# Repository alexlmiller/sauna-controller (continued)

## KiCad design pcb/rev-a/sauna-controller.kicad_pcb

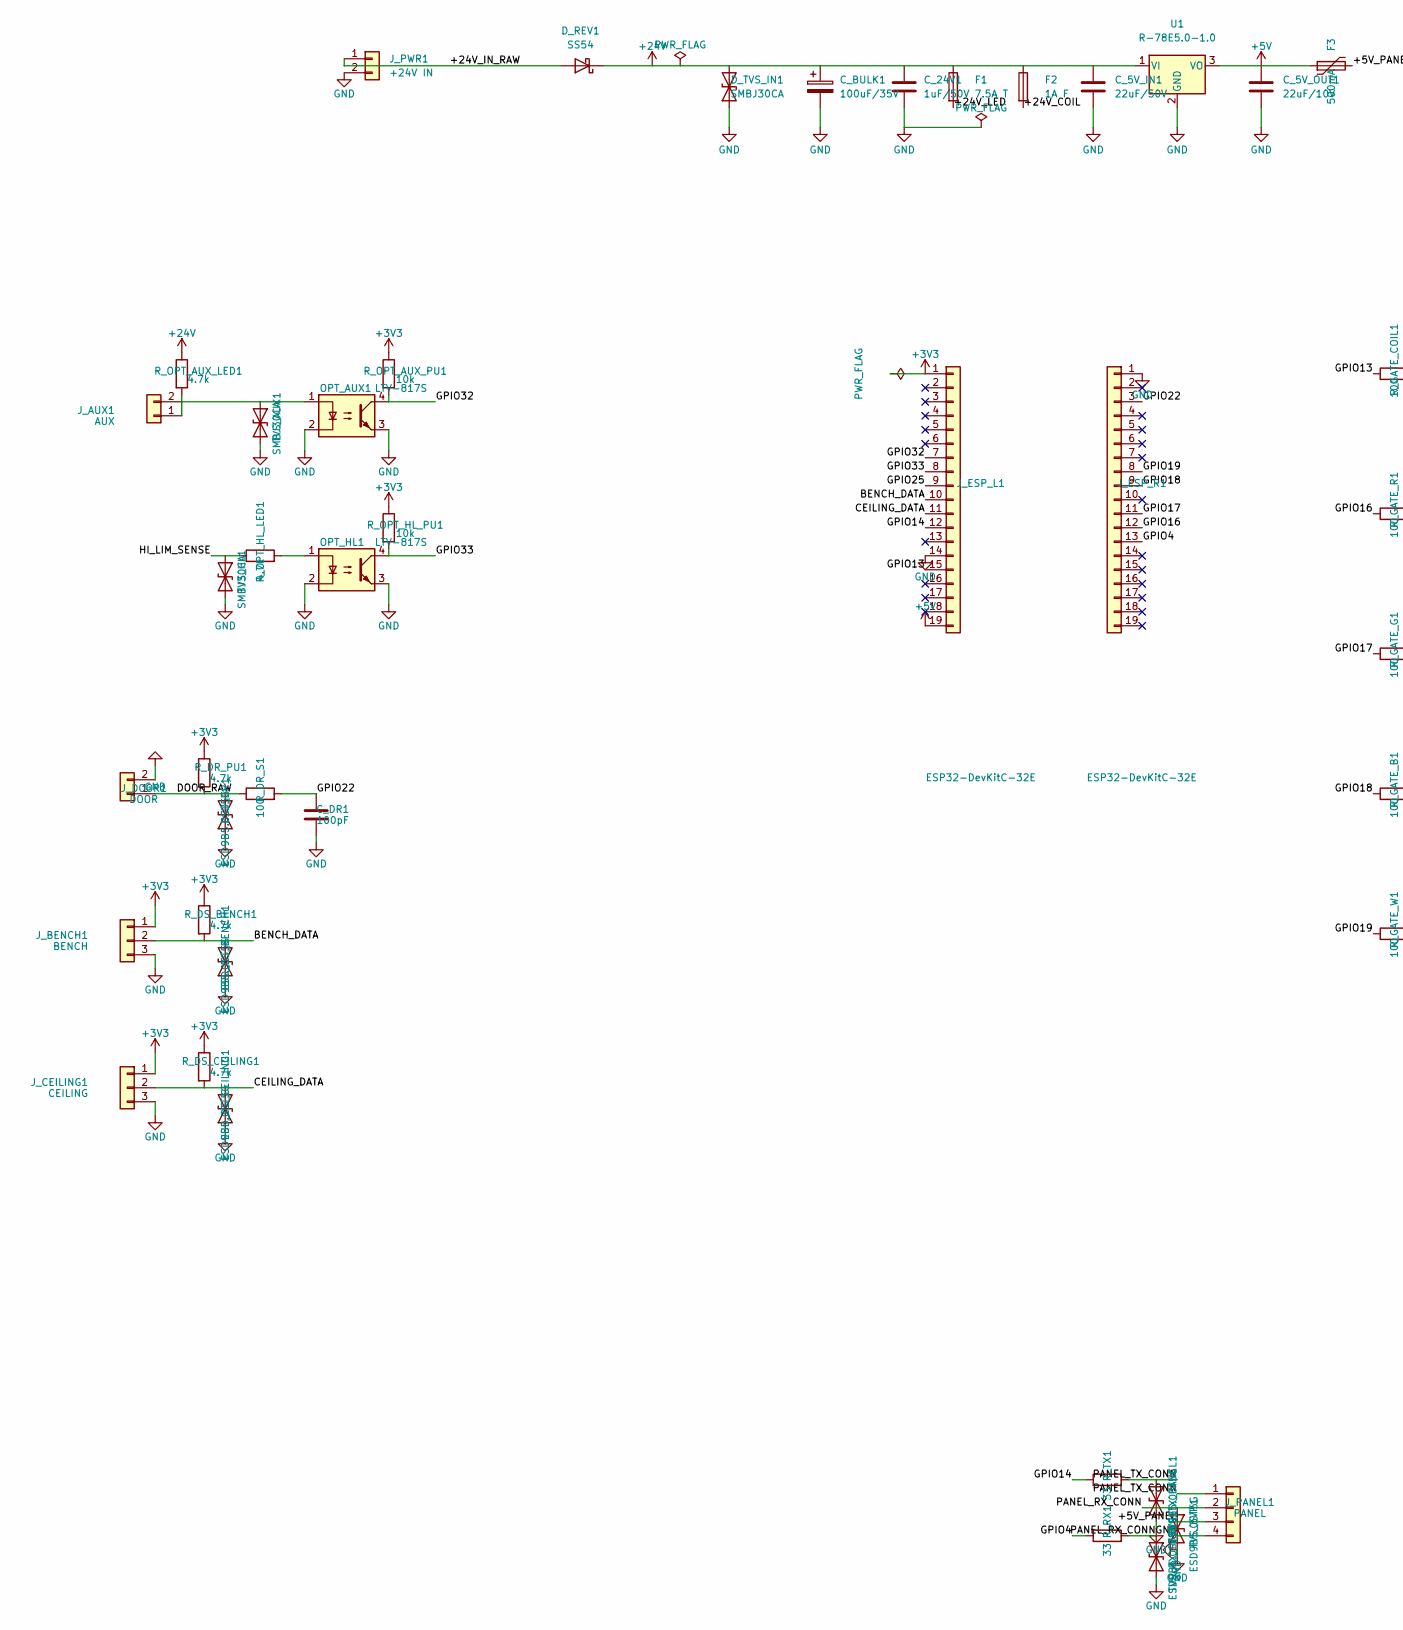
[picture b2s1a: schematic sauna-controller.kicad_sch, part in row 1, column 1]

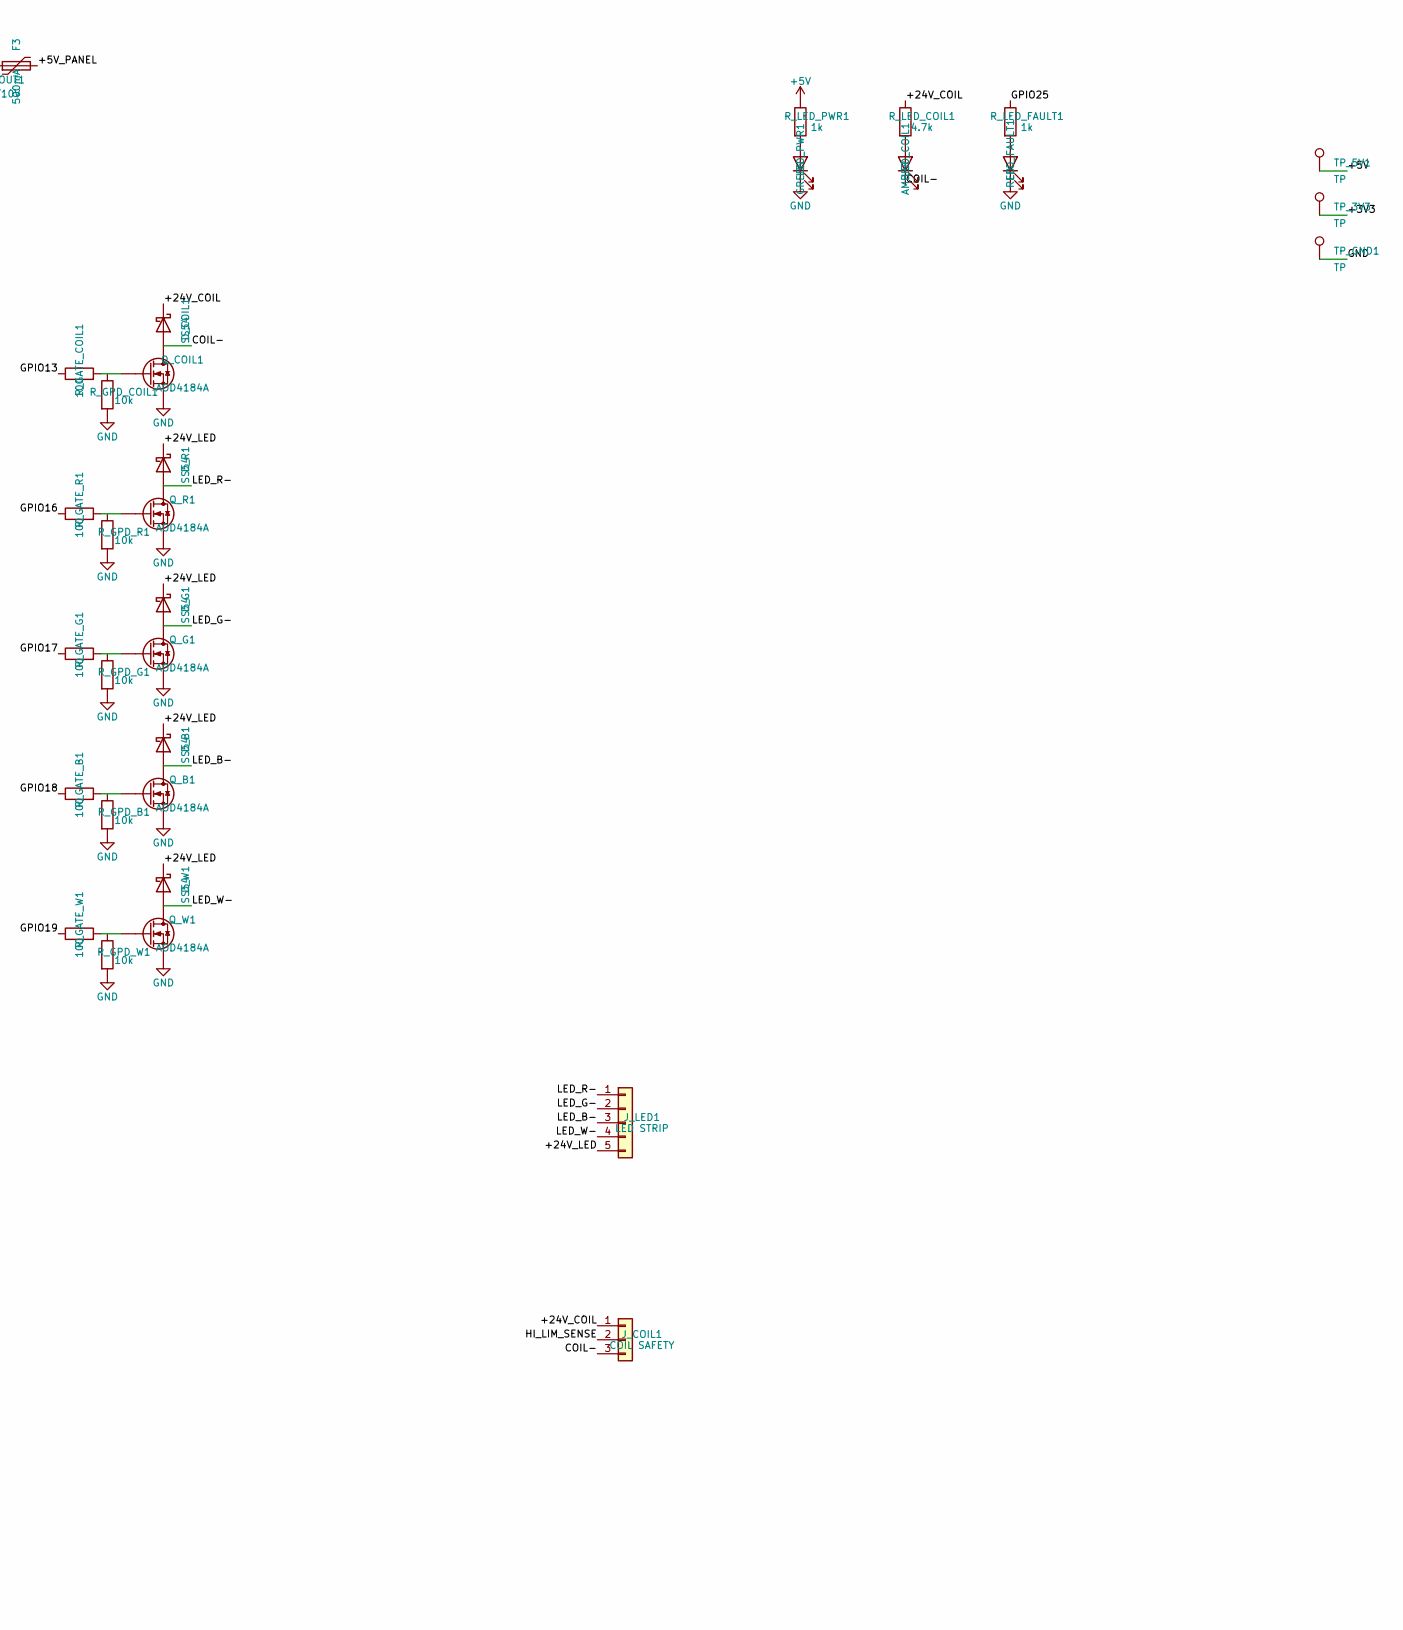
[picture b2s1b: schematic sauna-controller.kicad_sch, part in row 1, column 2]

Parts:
C_5V_IN1: 22uF/50V; C_1210_3225Metric
C_5V_OUT1: 22uF/10V; C_0805_2012Metric
C_24V1: 1uF/50V; C_0805_2012Metric
C_BULK1: 100uF/35V; CP_Radial_D8.0mm_P3.50mm
C_DR1: 100pF; C_0805_2012Metric
D_B1: SS54; D_SMA
D_COIL1: SS54; D_SMA
D_G1: SS54; D_SMA
D_R1: SS54; D_SMA
D_REV1: SS54; D_SMA
D_TVS_IN1: SMBJ30CA; D_SMB
D_W1: SS54; D_SMA
ESD_DR1: ESD9B5.0ST5G; D_SOD-323
ESD_DS_BENCH1: ESD9B5.0ST5G; D_SOD-323
ESD_DS_CEILING1: ESD9B5.0ST5G; D_SOD-323
F1: 7.5A T; Fuseholder_Clip-5x20mm_Schurter_OG_Lateral_P15.00x5.00mm_D1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
F2: 1A F; Fuseholder_Clip-5x20mm_Schurter_OG_Lateral_P15.00x5.00mm_D1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
F3: 500mA; R_1812_4532Metric
J_AUX1: AUX; TerminalBlock_Phoenix_MKDS-1,5-2-5.08_1x02_P5.08mm_Horizont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
J_BENCH1: BENCH; TerminalBlock_Phoenix_MKDS-1,5-3-5.08_1x03_P5.08mm_Horizont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
J_CEILING1: CEILING; TerminalBlock_Phoenix_MKDS-1,5-3-5.08_1x03_P5.08mm_Horizont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
J_COIL1: COIL SAFETY; TerminalBlock_Phoenix_MKDS-1,5-3-5.08_1x03_P5.08mm_Horizont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
J_DOOR1: DOOR; TerminalBlock_Phoenix_MKDS-1,5-2-5.08_1x02_P5.08mm_Horizont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
J_ESP_L1: ESP32-DevKitC-32E; PinSocket_1x19_P2.54mm_Vertical
J_ESP_R1: ESP32-DevKitC-32E; PinSocket_1x19_P2.54mm_Vertical
J_LED1: LED STRIP; TerminalBlock_Phoenix_MKDS-1,5-5-5.08_1x05_P5.08mm_Horizont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
J_PANEL1: PANEL; TerminalBlock_Phoenix_MKDS-1,5-4-5.08_1x04_P5.08mm_Horizont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
J_PWR1: +24V IN; TerminalBlock_Phoenix_MKDS-1,5-2-5.08_1x02_P5.08mm_Horizont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
LED_COIL1: AMBER; LED_0805_2012Metric
LED_FAULT1: RED; LED_0805_2012Metric
LED_PWR1: GREEN; LED_0805_2012Metric
OPT_AUX1: LTV-817S; DIP-4_W7.62mm
OPT_HL1: LTV-817S; DIP-4_W7.62mm
Q_B1: AOD4184A; TO-252-2
Q_COIL1: AOD4184A; TO-252-2
Q_G1: AOD4184A; TO-252-2
Q_R1: AOD4184A; TO-252-2
Q_W1: AOD4184A; TO-252-2
R_DR_PU1: 4.7k; R_0805_2012Metric
R_DR_S1: 100; R_0805_2012Metric
R_DS_BENCH1: 4.7k; R_0805_2012Metric
R_DS_CEILING1: 4.7k; R_0805_2012Metric
R_GATE_B1: 100; R_0805_2012Metric
R_GATE_COIL1: 100; R_0805_2012Metric
R_GATE_G1: 100; R_0805_2012Metric
R_GATE_R1: 100; R_0805_2012Metric
R_GATE_W1: 100; R_0805_2012Metric
R_GPD_B1: 10k; R_0805_2012Metric
R_GPD_COIL1: 10k; R_0805_2012Metric
R_GPD_G1: 10k; R_0805_2012Metric
R_GPD_R1: 10k; R_0805_2012Metric
R_GPD_W1: 10k; R_0805_2012Metric
R_LED_COIL1: 4.7k; R_0805_2012Metric
R_LED_FAULT1: 1k; R_0805_2012Metric
R_LED_PWR1: 1k; R_0805_2012Metric
R_OPT_AUX_LED1: 4.7k; R_0805_2012Metric
R_OPT_AUX_PU1: 10k; R_0805_2012Metric
R_OPT_HL_LED1: 4.7k; R_0805_2012Metric
R_OPT_HL_PU1: 10k; R_0805_2012Metric
R_RX1: 33; R_0805_2012Metric
R_TX1: 33; R_0805_2012Metric
TP_3V3, TP_5V1: TP; TestPoint_Pad_D1.5mm
TP_GND1: TP; TestPoint_Pad_D1.5mm
TVS_5VP1: ESD9B5.0ST5G; D_SOD-323
TVS_AUX1: SMBJ30CA; D_SMB
TVS_HL1: SMBJ30CA; D_SMB
TVS_RX_PANEL1: ESD9B5.0ST5G; D_SOD-323
TVS_TX_PANEL1: ESD9B5.0ST5G; D_SOD-323
U1: R-78E5.0-1.0; Converter_DCDC_RECOM_R-78E-0.5_THT

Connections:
+3V3: J_BENCH1.1, J_CEILING1.1, J_ESP_L1.1, R_DR_PU1.1, R_DS_BENCH1.1, R_DS_CEILING1.1, R_OPT_AUX_PU1.1, R_OPT_HL_PU1.1, TP_3V3.1 (1_1)
+5V: C_5V_OUT1.1, F3.1, J_ESP_L1.19, R_LED_PWR1.1, TP_5V1.1 (1_1), U1.3 (VO)
+24V: C_5V_IN1.1, C_24V1.1, C_BULK1.1, D_REV1.1 (K), D_TVS_IN1.2 (A2), F1.1, F2.1, R_OPT_AUX_LED1.1, U1.1 (VI)
/+5V_PANEL: F3.2, J_PANEL1.3
/+24V_COIL: D_COIL1.1 (K), F2.2, J_COIL1.1, R_LED_COIL1.1
/+24V_IN_RAW: D_REV1.2 (A), J_PWR1.1
/+24V_LED: D_B1.1 (K), D_G1.1 (K), D_R1.1 (K), D_W1.1 (K), F1.2, J_LED1.5
/BENCH_DATA: ESD_DS_BENCH1.2 (A2), J_BENCH1.2, J_ESP_L1.10, R_DS_BENCH1.2
/CEILING_DATA: ESD_DS_CEILING1.2 (A2), J_CEILING1.2, J_ESP_L1.11, R_DS_CEILING1.2
/COIL-: D_COIL1.2 (A), J_COIL1.3, LED_COIL1.1 (K), Q_COIL1.2 (D)
/DOOR_RAW: ESD_DR1.2 (A2), J_DOOR1.1, R_DR_PU1.2, R_DR_S1.1
/GPIO4: J_ESP_R1.13, R_RX1.1
/GPIO13: J_ESP_L1.15, R_GATE_COIL1.1
/GPIO14: J_ESP_L1.12, R_TX1.1
/GPIO16: J_ESP_R1.12, R_GATE_R1.1
/GPIO17: J_ESP_R1.11, R_GATE_G1.1
/GPIO18: J_ESP_R1.9, R_GATE_B1.1
/GPIO19: J_ESP_R1.8, R_GATE_W1.1
/GPIO22: C_DR1.1, J_ESP_R1.3, R_DR_S1.2
/GPIO25: J_ESP_L1.9, R_LED_FAULT1.1
/GPIO32: J_ESP_L1.7, OPT_AUX1.4, R_OPT_AUX_PU1.2
/GPIO33: J_ESP_L1.8, OPT_HL1.4, R_OPT_HL_PU1.2
/HI_LIM_SENSE: J_COIL1.2, R_OPT_HL_LED1.1, TVS_HL1.1 (A1)
/LED_B-: D_B1.2 (A), J_LED1.3, Q_B1.2 (D)
/LED_G-: D_G1.2 (A), J_LED1.2, Q_G1.2 (D)
/LED_R-: D_R1.2 (A), J_LED1.1, Q_R1.2 (D)
/LED_W-: D_W1.2 (A), J_LED1.4, Q_W1.2 (D)
/PANEL_RX_CONN: J_PANEL1.2, R_RX1.2, TVS_5VP1.1 (A1), TVS_RX_PANEL1.1 (A1)
/PANEL_TX_CONN: J_PANEL1.1, R_TX1.2, TVS_TX_PANEL1.1 (A1)
GND: C_5V_IN1.2, C_5V_OUT1.2, C_24V1.2, C_BULK1.2, C_DR1.2, D_TVS_IN1.1 (A1), ESD_DR1.1 (A1), ESD_DS_BENCH1.1 (A1), ESD_DS_CEILING1.1 (A1), J_BENCH1.3, J_CEILING1.3, J_DOOR1.2, J_ESP_L1.14, J_ESP_R1.1, J_PANEL1.4, J_PWR1.2, LED_FAULT1.1 (K), LED_PWR1.1 (K), OPT_AUX1.2, OPT_AUX1.3, OPT_HL1.2, OPT_HL1.3, Q_B1.3 (S), Q_COIL1.3 (S), Q_G1.3 (S), Q_R1.3 (S), Q_W1.3 (S), R_GPD_B1.2, R_GPD_COIL1.2, R_GPD_G1.2, R_GPD_R1.2, R_GPD_W1.2, TP_GND1.1 (1_1), TVS_5VP1.2 (A2), TVS_AUX1.2 (A2), TVS_HL1.2 (A2), TVS_RX_PANEL1.2 (A2), TVS_TX_PANEL1.2 (A2), U1.2 (GND)
unnamed: J_AUX1.1, R_OPT_AUX_LED1.2
unnamed: J_AUX1.2, OPT_AUX1.1, TVS_AUX1.1 (A1)
unnamed: LED_COIL1.2 (A), R_LED_COIL1.2
unnamed: LED_FAULT1.2 (A), R_LED_FAULT1.2
unnamed: LED_PWR1.2 (A), R_LED_PWR1.2
unnamed: OPT_HL1.1, R_OPT_HL_LED1.2
unnamed: Q_B1.1 (G), R_GATE_B1.2, R_GPD_B1.1
unnamed: Q_COIL1.1 (G), R_GATE_COIL1.2, R_GPD_COIL1.1
unnamed: Q_G1.1 (G), R_GATE_G1.2, R_GPD_G1.1
unnamed: Q_R1.1 (G), R_GATE_R1.2, R_GPD_R1.1
unnamed: Q_W1.1 (G), R_GATE_W1.2, R_GPD_W1.1

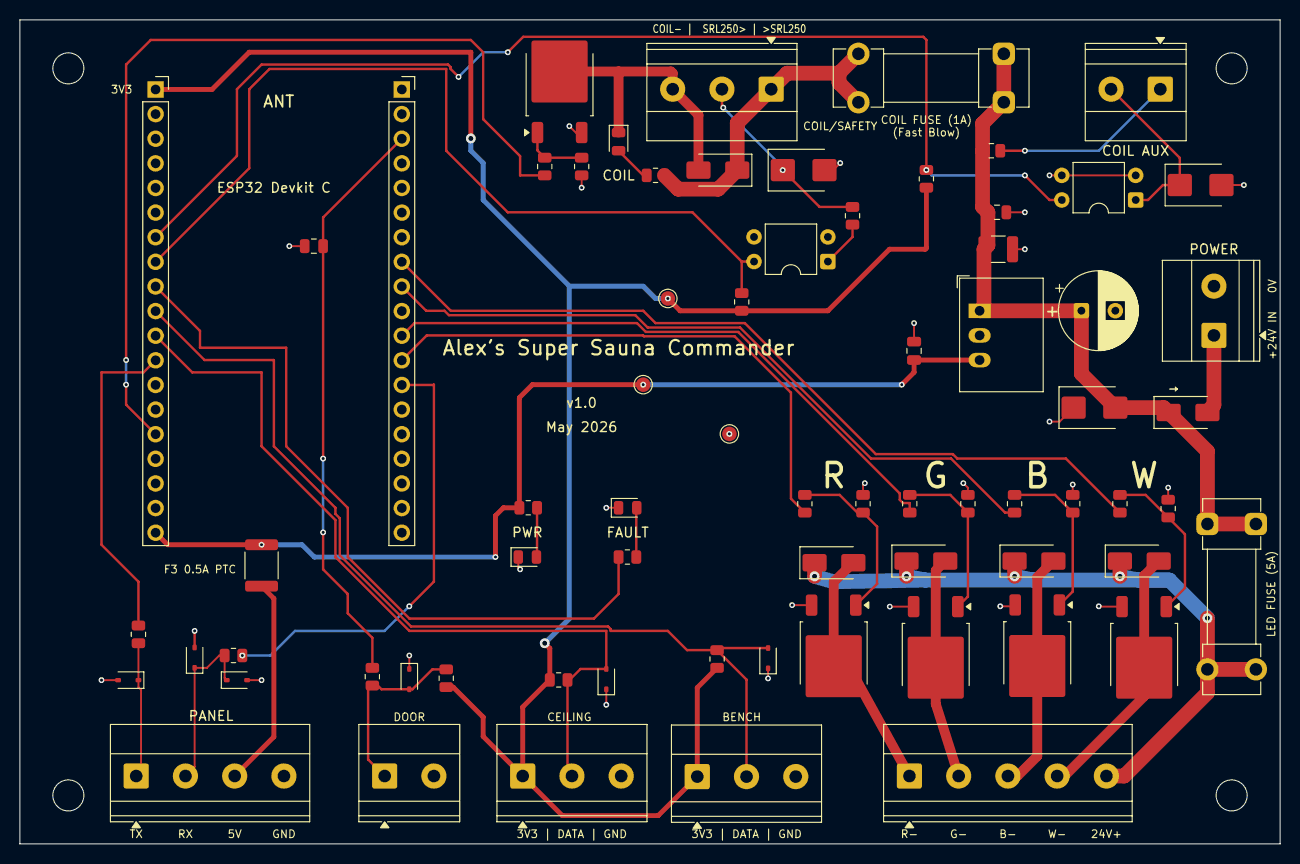
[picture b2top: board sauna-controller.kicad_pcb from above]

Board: 2 copper layers, 130.0 x 85.0 mm, 74 parts (0 on the bottom side), 41 nets.

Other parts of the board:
MH1, MH2, MH3, MH4: MountingHole_3.2mm_M3; MountingHole_3.2mm_M3_DIN965

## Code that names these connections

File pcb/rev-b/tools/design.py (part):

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    "RELAY_FB_IN": "SIGNAL",
    "RELAY_FB_LED": "SIGNAL",
    "HL_LED": "SIGNAL",
    "GPIO16": "SIGNAL",
    "GPIO17": "SIGNAL",
    "GPIO18": "SIGNAL",
    "GPIO19": "SIGNAL",
    "GPIO22": "SIGNAL",
    "GPIO23": "SIGNAL",
    "GPIO25": "SIGNAL",
    "GPIO26": "SIGNAL",
    "GPIO27": "SIGNAL",
    "GPIO32": "SIGNAL",
    "GPIO33": "SIGNAL",
    "GPIO34": "SIGNAL",
    "GPIO35": "SIGNAL",
    "GPIO4": "SIGNAL",
    "G_COIL": "SIGNAL",
    "G_AUX": "SIGNAL",
    "G_R": "SIGNAL",
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
# --- Optional AUX 24 V low-side output scaffold ----------------------------
# This output is intentionally placed off the right side of the board for now.
# Drag/place/route it in KiCad once the final Rev B floorplan has room. GPIO4
# is ESP32 DevKitC row GND/GPIO23 pin 13.
add("F4", "POLYFUSE", "PTC_2920", "2A PTC (AUX)", (86.692, 14.122, -90),
    {1: "+24V", 2: "+24V_AUX"}, (55, 85),
    MPN="JLC C139284")
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add("Q6", "NMOS", "TO252", "AOD4184A", (100.092, 28.988, -90),
    {1: "G_AUX", 2: "AUX_OUT-", 3: "GND"}, (116, 190), MPN="AOD4184A")
add("R32", "R", "R_0805", "100R", (92.28, 28.8, 90),
    {1: "GPIO4", 2: "G_AUX"}, (108, 180))
add("R33", "R", "R_0805", "10K", (95.394, 23.654, 0),
    {1: "G_AUX", 2: "GND"}, (120, 180))

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add("Q1", "NMOS", "TO252", "AOD4184A", (114.91, 25.91, 270),
    {1: "G_COIL", 2: "COIL-", 3: "GND"}, (90, 160), MPN="AOD4184A")
add("R7", "R", "R_0805", "100R", (104.538, 43.466, 0),
    {1: "GPIO23", 2: "G_COIL"}, (84, 150))
add("R12", "R", "R_0805", "10K", (104.538, 39.148, 180),
    {1: "G_COIL", 2: "GND"}, (96, 150))

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add("Q5", "NMOS", "TO252", "AOD4184A", (49, 18, 0),
    {1: "G_W", 2: "LED_W-", 3: "GND"}, (210, 160), MPN="AOD4184A")
add("R8", "R", "R_0805", "100R", (23.7, 26.5, 90),
    {1: "GPIO19", 2: "G_R"}, (144, 150))
add("R9", "R", "R_0805", "100R", (32.59, 26.5, 90),
    {1: "GPIO18", 2: "G_G"}, (164, 150))
add("R10", "R", "R_0805", "100R", (41.59, 26.5, 90),
    {1: "GPIO17", 2: "G_B"}, (184, 150))
add("R11", "R", "R_0805", "100R", (50.59, 26.5, 90),
    {1: "GPIO16", 2: "G_W"}, (204, 150))
add("R13", "R", "R_0805", "10K", (23.7, 30.5, 90),
    {1: "G_R", 2: "GND"}, (156, 150))
add("R14", "R", "R_0805", "10K", (32.59, 30.5, 90),
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add("D9", "D", "D_SOD323", "1N4148WS", (92.28, 57.69, 0),
    {1: "RELAY_FB_LED", 2: "GND"}, (132, 90))
add("OPT_RELAY_FB", "OPTO", "SOP4_OPTO", "LTV-817S", (91.255, 55.13, 90),
    {1: "RELAY_FB_LED", 2: "GND", 3: "GND", 4: "GPIO34"}, (150, 80),
    MPN="LTV-817S")
add("R4", "R", "R_0805", "10K", (82.12, 57.37, 90),
    {1: "+3V3", 2: "GPIO34"}, (162, 70))
# High-limit channel: senses 24 V presence on SRL250_RTN (post-high-limit).
add("R2", "R", "R_1206", "3K3", (118.95, 71.66, 180),
    {1: "SRL250_RTN", 2: "HL_LED"}, (126, 110))
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add("D10", "D", "D_SOD323", "1N4148WS", (108.79, 52.61, 0),
    {1: "HL_LED", 2: "GND"}, (132, 124))
add("OPT2", "OPTO", "SOP4_OPTO", "LTV-817S", (91.255, 65.29, 90),
    {1: "HL_LED", 2: "GND", 3: "GND", 4: "GPIO35"}, (150, 110),
    MPN="LTV-817S")
add("R5", "R", "R_0805", "10K", (82.12, 66.006, 90),
    {1: "+3V3", 2: "GPIO35"}, (162, 100))
# (Spare opto channel removed -- not needed. Its former D11 reference is now
#  reused by the optional AUX flyback diode.)

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add("D6", "ESD", "D_SOD923", "ESD9B5.0", (39.22, 73.876, 180),
    {1: "DOOR_IN", 2: "GND"}, (276, 80), MPN="ESD9B5.0ST5G")
add("R18", "R", "R_0805", "1K", (42.05, 73.946, 0),
    {1: "DOOR_IN", 2: "GPIO25"}, (282, 76))
add("C9", "C", "C_0805", "100nF", (46.05, 73.946, 0),
    {1: "GPIO25", 2: "GND"}, (288, 86))
add("R17", "R", "R_0805", "10K", (50.05, 73.946, 0),
    {1: "+3V3", 2: "GPIO25"}, (294, 70))

# --- DS18B20 1-Wire (bottom band, above J_BENCH / J_CEILING) ----------------
add("R19", "R", "R_0805", "4K7", (55.45, 73.88, 90),
    {1: "+3V3", 2: "BENCH_DATA"}, (276, 106))
add("R21", "R", "R_0805", "100R", (57.99, 73.88, 90),
    {1: "BENCH_DATA", 2: "GPIO26"}, (282, 110))
add("D7", "ESD", "D_SOD923", "ESD9B5.0", (61.03, 74.2, 0),
    {1: "BENCH_DATA", 2: "GND"}, (288, 116), MPN="ESD9B5.0ST5G")
add("R20", "R", "R_0805", "4K7", (78, 73, 0),
    {1: "+3V3", 2: "CEIL_DATA"}, (276, 136))
add("R22", "R", "R_0805", "100R", (82, 73, 0),
    {1: "CEIL_DATA", 2: "GPIO27"}, (282, 140))
add("D8", "ESD", "D_SOD923", "ESD9B5.0", (86, 73, 0),
    {1: "CEIL_DATA", 2: "GND"}, (288, 146), MPN="ESD9B5.0ST5G")

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     4: "PANEL_RX", 5: "+3V3", 6: "PANEL_TX"}, (240, 70),
    MPN="USBLC6-2SC6")
add("R23", "R", "R_0805", "100R", (24.97, 74.52, -90),
    {1: "GPIO32", 2: "PANEL_TX"}, (228, 60))
add("R24", "R", "R_0805", "100R", (27.51, 74.52, 90),
    {1: "PANEL_RX", 2: "GPIO33"}, (228, 66))

# --- Indicators (top-right corner, above J_COIL) ----------------------------
add("R25", "R", "R_0805", "10K", (107.555, 10.828, 0),
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add("LED2", "LED", "LED_0805", "GREEN 5V", (112.555, 14.828, 0),
    {1: "LED5_A", 2: "GND"}, (40, 140))
add("R27", "R", "R_0805", "1K", (107.555, 18.828, 0),
    {1: "GPIO22", 2: "FAULT_A"}, (58, 130))
add("LED3", "LED", "LED_0805", "RED FAULT", (112.555, 18.828, 0),
    {1: "FAULT_A", 2: "GND"}, (58, 140))

# --- ESP32 DevKitC v4 socket (2x 1x19 female, 25.4 mm row spacing) ----------
# Antenna points LEFT (-x). Row A (y=44) = DevKitC "GND/GPIO23" column,
# Row B (y=69.4) = DevKitC "3V3" column. Pin 1 of both rows at antenna end.
ESP2_PINS = {1: "GND", 2: "GPIO23", 3: "GPIO22", 4: None, 5: None, 6: None,
             7: "GND", 8: "GPIO19", 9: "GPIO18", 10: None, 11: "GPIO17",
             12: "GPIO16", 13: "GPIO4", 14: None, 15: None, 16: None,
             17: None, 18: None, 19: None}
ESP1_PINS = {1: "+3V3", 2: None, 3: None, 4: None, 5: "GPIO34", 6: "GPIO35",
             7: "GPIO32", 8: "GPIO33", 9: "GPIO25", 10: "GPIO26",
             11: "GPIO27", 12: None, 13: None, 14: "GND", 15: None,
             16: None, 17: None, 18: None, 19: "+5V"}
add("J_ESP2", "CONN19", "SOCKET_1x19", "ESP_ROW_GND23", (30, 44, 0),
    ESP2_PINS, (330, 40), MPN="PinSocket 1x19 2.54mm")
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
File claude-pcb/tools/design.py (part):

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    "HL_LED": "SIGNAL",
    "SPARE_IN": "SIGNAL",
    "SPARE_LED": "SIGNAL",
    "GPIO13": "SIGNAL",
    "GPIO16": "SIGNAL",
    "GPIO17": "SIGNAL",
    "GPIO18": "SIGNAL",
    "GPIO19": "SIGNAL",
    "GPIO22": "SIGNAL",
    "GPIO23": "SIGNAL",
    "GPIO25": "SIGNAL",
    "GPIO26": "SIGNAL",
    "GPIO27": "SIGNAL",
    "GPIO32": "SIGNAL",
    "GPIO33": "SIGNAL",
    "GPIO14": "SIGNAL",
    "GPIO4": "SIGNAL",
    "G_COIL": "SIGNAL",
    "G_R": "SIGNAL",
    "G_G": "SIGNAL",
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add("Q1", "NMOS", "TO252", "AOD4184A", (110, 28, 0),
    {1: "G_COIL", 2: "COIL-", 3: "GND"}, (90, 160), MPN="AOD4184A")
add("R7", "R", "R_0805", "100R", (102, 26, 90),
    {1: "GPIO13", 2: "G_COIL"}, (84, 150))
add("R12", "R", "R_0805", "10K", (105, 26, 90),
    {1: "G_COIL", 2: "GND"}, (96, 150))

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add("Q5", "NMOS", "TO252", "AOD4184A", (49, 18, 0),
    {1: "G_W", 2: "LED_W-", 3: "GND"}, (210, 160), MPN="AOD4184A")
add("R8", "R", "R_0805", "100R", (22, 26.5, 90),
    {1: "GPIO19", 2: "G_R"}, (144, 150))
add("R9", "R", "R_0805", "100R", (31, 26.5, 90),
    {1: "GPIO18", 2: "G_G"}, (164, 150))
add("R10", "R", "R_0805", "100R", (40, 26.5, 90),
    {1: "GPIO17", 2: "G_B"}, (184, 150))
add("R11", "R", "R_0805", "100R", (49, 26.5, 90),
    {1: "GPIO16", 2: "G_W"}, (204, 150))
add("R13", "R", "R_0805", "10K", (22, 30.5, 90),
    {1: "G_R", 2: "GND"}, (156, 150))
add("R14", "R", "R_0805", "10K", (31, 30.5, 90),
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add("D9", "D", "D_SOD323", "1N4148WS", (112, 46, 0),
    {1: "AUX_LED", 2: "GND"}, (132, 90))
add("OPT1", "OPTO", "DIP4", "LTV-817", (105, 48, 0),
    {1: "AUX_LED", 2: "GND", 3: "GND", 4: "GPIO32"}, (150, 80),
    MPN="LTV-817")
add("R4", "R", "R_0805", "10K", (99, 53, 0),
    {1: "+3V3", 2: "GPIO32"}, (162, 70))
# High-limit channel: senses 24 V presence on SRL250_RTN (post-high-limit).
add("R2", "R", "R_1206", "3K3 1W", (116, 62, 0),
    {1: "SRL250_RTN", 2: "HL_LED"}, (126, 110))
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add("D10", "D", "D_SOD323", "1N4148WS", (112, 64, 0),
    {1: "HL_LED", 2: "GND"}, (132, 124))
add("OPT2", "OPTO", "DIP4", "LTV-817", (105, 66, 0),
    {1: "HL_LED", 2: "GND", 3: "GND", 4: "GPIO33"}, (150, 110),
    MPN="LTV-817")
add("R5", "R", "R_0805", "10K", (99, 71, 0),
    {1: "+3V3", 2: "GPIO33"}, (162, 100))
# Spare channel (GPIO25, matches commented-out firmware block).
add("R3", "R", "R_1206", "3K3 1W", (88, 57, 0),
    {1: "SPARE_IN", 2: "SPARE_LED"}, (126, 140))
add("D4", "TVS", "D_SMB", "SMBJ30CA", (88, 63, 90),
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add("D11", "D", "D_SOD323", "1N4148WS", (75, 57, 0),
    {1: "SPARE_LED", 2: "GND"}, (132, 154))
add("OPT3", "OPTO", "DIP4", "LTV-817", (81, 60, 0),
    {1: "SPARE_LED", 2: "GND", 3: "GND", 4: "GPIO25"}, (150, 140),
    MPN="LTV-817")
add("R6", "R", "R_0805", "10K", (75, 63, 0),
    {1: "+3V3", 2: "GPIO25"}, (162, 130))

# --- Door input (bottom band, above J_DOOR) ---------------------------------
add("D6", "ESD", "D_SOD923", "ESD9B5.0", (37, 73, 0),
    {1: "DOOR_IN", 2: "GND"}, (276, 80), MPN="ESD9B5.0ST5G")
add("R18", "R", "R_0805", "1K", (41, 73, 0),
    {1: "DOOR_IN", 2: "GPIO22"}, (282, 76))
add("C9", "C", "C_0805", "100nF", (45, 73, 0),
    {1: "GPIO22", 2: "GND"}, (288, 86))
add("R17", "R", "R_0805", "10K", (49, 73, 0),
    {1: "+3V3", 2: "GPIO22"}, (294, 70))

# --- DS18B20 1-Wire (bottom band, above J_BENCH / J_CEILING) ----------------
add("R19", "R", "R_0805", "4K7", (53, 73, 0),
    {1: "+3V3", 2: "BENCH_DATA"}, (276, 106))
add("R21", "R", "R_0805", "100R", (57, 73, 0),
    {1: "BENCH_DATA", 2: "GPIO26"}, (282, 110))
add("D7", "ESD", "D_SOD923", "ESD9B5.0", (61, 73, 0),
    {1: "BENCH_DATA", 2: "GND"}, (288, 116), MPN="ESD9B5.0ST5G")
add("R20", "R", "R_0805", "4K7", (78, 73, 0),
    {1: "+3V3", 2: "CEIL_DATA"}, (276, 136))
add("R22", "R", "R_0805", "100R", (82, 73, 0),
    {1: "CEIL_DATA", 2: "GPIO27"}, (282, 140))
add("D8", "ESD", "D_SOD923", "ESD9B5.0", (86, 73, 0),
    {1: "CEIL_DATA", 2: "GND"}, (288, 146), MPN="ESD9B5.0ST5G")

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     4: "PANEL_RX", 5: "+3V3", 6: "PANEL_TX"}, (240, 70),
    MPN="USBLC6-2SC6")
add("R23", "R", "R_0805", "100R", (40, 53, 0),
    {1: "GPIO14", 2: "PANEL_TX"}, (228, 60))
add("R24", "R", "R_0805", "100R", (52, 53, 0),
    {1: "PANEL_RX", 2: "GPIO4"}, (228, 66))

# --- Indicators (top-right corner, above J_COIL) ----------------------------
add("R25", "R", "R_0805", "10K", (104, 7, 0),
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add("LED2", "LED", "LED_0805", "GREEN 5V", (109, 11, 0),
    {1: "LED5_A", 2: "GND"}, (40, 140))
add("R27", "R", "R_0805", "1K", (104, 15, 0),
    {1: "GPIO23", 2: "FAULT_A"}, (58, 130))
add("LED3", "LED", "LED_0805", "RED FAULT", (109, 15, 0),
    {1: "FAULT_A", 2: "GND"}, (58, 140))

# --- ESP32 DevKitC v4 socket (2x 1x19 female, 25.4 mm row spacing) ----------
# Antenna points LEFT (-x). Row A (y=44) = DevKitC "GND/GPIO23" column,
# Row B (y=69.4) = DevKitC "3V3" column. Pin 1 of both rows at antenna end.
ESP2_PINS = {1: "GND", 2: "GPIO23", 3: "GPIO22", 4: None, 5: None, 6: None,
             7: "GND", 8: "GPIO19", 9: "GPIO18", 10: None, 11: "GPIO17",
             12: "GPIO16", 13: "GPIO4", 14: None, 15: None, 16: None,
             17: None, 18: None, 19: None}
ESP1_PINS = {1: "+3V3", 2: None, 3: None, 4: None, 5: None, 6: None,
             7: "GPIO32", 8: "GPIO33", 9: "GPIO25", 10: "GPIO26",
             11: "GPIO27", 12: "GPIO14", 13: None, 14: "GND", 15: "GPIO13",
             16: None, 17: None, 18: None, 19: "+5V"}
add("J_ESP2", "CONN19", "SOCKET_1x19", "ESP_ROW_GND23", (30, 44, 0),
    ESP2_PINS, (330, 40), MPN="PinSocket 1x19 2.54mm")
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        ("TP3", "+3V3", (40, 64)), ("TP4", "GND", (45, 12)),
        ("TP5", "LED_R-", (20, 4.5)), ("TP6", "LED_G-", (29, 4.5)),
        ("TP7", "LED_B-", (38, 4.5)), ("TP8", "LED_W-", (47, 4.5)),
        ("TP9", "COIL-", (118, 34)), ("TP10", "GPIO32", (95, 48)),
        ("TP11", "GPIO33", (95, 66)), ("TP12", "GPIO22", (54, 64)),
        ("TP13", "PANEL_TX", (40, 49)), ("TP14", "PANEL_RX", (54, 58)),
        ("TP15", "AUX_LED", (111, 42))]
for i, (ref, net, at) in enumerate(_tps):
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
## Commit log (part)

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2025-08-11 Update README.md
    Update README with overview and hardware information
2025-08-11 Add initial ESP Firmware
    Create sauna-controller.yaml with the firmware configuration for the ESP board
2025-08-16 Update sauna-controller.yaml
    Fixed platform specific issues and validated in ESPHome
2025-08-16 Move connections off strapped GPIO Pins
2025-08-16 Update README.md to match YAML changes
2025-09-27 Update sauna-controller.yaml
    final working code - fixed temp sensor issues and updated GPIO pin locations for cleanest wiring
2025-09-27 Update wiring plan & notes in README
2025-09-30 extend thermostat cycle times
    changed thermostant min cycle time from 2 minutes > 5 minutes to prevent unnecessary wear on heater
2025-11-07 change from PT100s to DS18B20 Temp Sensors
2025-11-11 Update sauna-controller.yaml to reflect updating wiring
2025-11-11 Add "final" version of code
    mostly final code with all core features and safeties enabled
2025-11-12 Update README.md
    moved door sensor to pin 22
2026-06-11 Document PCB bring-up notes
2026-06-13 Add Rev B PCB design: gap analysis, full schematic, routed board
    - REV-B-DESIGN-REVIEW.md: review of all existing Rev B planning docs with
    issues found (undersized 5V regulator, Rev A AUX opto failure analysis,
    fuse footprint mismatch, high-limit polarity ambiguity, stale RS-485/
    fuse references) and the decisions taken for each
    - FIRMWARE-CHANGES.md: LED PWM GPIO remap (crossing-free gate routing),
    FAULT LED on GPIO23, high-limit comment fix, spare opto input
2026-06-13 Rearrange Rev B board: coil/aux on right edge, SRL bottom-right
    Re-floorplan so connectors follow the physical harness, with the
    contactor located to the right of the board:
    - J_COIL, J_AUX moved to the right edge (next to the contactor)
    - J_SRL250 to the right side of the bottom edge (sauna-room harness)
    - J_PWR stays on the top edge; fuse bank below it
    - J_LED to the left edge (upper-left, above the antenna keepout)
2026-06-17 chore(pcb): archive Rev A board files
2026-06-17 feat(pcb): add Rev B control board design
2026-06-17 chore(pcb): add Rev B fabrication outputs
2026-06-17 feat(firmware): split Rev B control board and wall panel configs
2026-06-17 docs: simplify Rev B build documentation
2026-06-17 chore(pcb): refresh Rev B fabrication outputs
